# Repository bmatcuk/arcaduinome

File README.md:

# arcaduinome
Arcaduinome is an [Arduino](http://www.arduino.cc/) based MIDI controller that uses arcade buttons for input. The name is a combination of Arcade, Arduino, and [Monome](http://monome.org/).

1. [Software](#software)
2. [Hardware](#hardware)
  1. [Schematic](#schematic)
  2. [Board PCB Layout](#board-pcb-layout)
3. [Arduino Firmware](#arduino-firmware)
4. [License](#license)

## Software
The ArduinoSketch directory contains the Arduino source code. It requires that you have the MIDI Library installed. The latest build (at time of writing) is included in this repo. You'll first need to install it into your Arduino app: Open the Arduino application and select Sketch -> Import Library -> Add Library, then select Arduino_MIDI_Library_v4.1.zip.

## Hardware
Arcaduinome is based around the [Arduino Uno](http://arduino.cc/en/Main/ArduinoBoardUno), third revision. Most of the other hardware components are to support the LEDs which light the arcade buttons. Each component links to a website where you could buy the part, but you can probably find most of these parts at a variety of distributors. A lot of these parts could be swapped out for similar parts. I've made some notes below about why I've chosen a specific part and whether or not you can use some other generic part.

Datasheets for some of these parts can be found in the `reference` directory of this repository.

* **[Arduino Uno R3](http://www.adafruit.com/products/50)**
    I highly recommend a 3rd Revision (R3) board here. The R3 board has a larger USB-to-serial microcontroller (Atmega16U2) which will be reprogrammed later. If you have an older R1 or R2 board, you'll need to reprogram the USB-to-serial microcontroller every time you need to switch between MIDI and Arduino mode. Very annoying. With the R3, you just jumper two pins to switch back to Arduino mode.

* **16x [Sanwa OBSC 24 CW](http://www.paradisearcadeshop.com/sanwa-obsc-24mm-translucent-pushbuttons/689-sanwa-obsc-24-cw.html)**
    Any arcade button will do. Sanwa buttons are extremely popular with arcade cabinet and fighting game enthusiasts for their quick response and high-reliability. However, the buttons might be the most expensive part, so you can save a bit with some cheaper buttons. Just make sure they are translucent/transparent.

* **[Protoshield for Arduino](http://www.adafruit.com/products/51)**
    This part is optional. I like using the protoshield to break out the IO pins from the Arduino and it gives me a nice area to solder everything together. Plus, it's compact.

* **16x [Common Anode RGB LEDs](http://www.adafruit.com/products/302)**
    Theoretically, any RGB LEDs will do, as long as they are common-anode. You may need to adjust resistor values depending on the forward voltage of the LEDs you pick. Link goes to a 25-pack that's actually cheaper, I've found, than buying 16 discrete LEDs from other distributors. So save some money and you'll have 9 extra LEDs for your next project! Woot!

* **[Sanken SLA5086 - 5x P-Channel FET Array](http://www.digikey.com/product-search/en?pv606=52&pv69=80&FV=fff40015%2Cfff80346&mnonly=0&newproducts=0&ColumnSort=0&page=1&stock=1&quantity=0&ptm=0&fid=0&pageSize=500)**
    The P-Channel FETs are used on the "high-side" of the LEDs to turn on the "rows". FETs are well-suited for this switching application, specifically P-Channels for the high-side. If every LED in a row is turned on, the high-side switch must be able to source ~0.24A. This part can handle 5A, so no problems there. Additionally, this particular part has a low (logic level) gate-threshold voltage, which means that it should fully "turn on" easily from the Arduino IO pin. All around, a good fit, and the hardest part to find alternatives for, unless you don't mind dealing with surface mount components. We're only going to use 4 of the 5 PFETs in this package, since we only have 4 rows of LEDs. And we're also going to use these rows to multiplex our buttons. This way, we only need to use 4 inputs for the 16 buttons.

* **2x [STMicroelectronics STPIC6D595B1R 8-bit Shift Register](http://www.digikey.com/product-detail/en/STPIC6D595B1R/497-6328-5-ND/1762207)**
    The shift registers are used on the "low-side" of the LEDs to control individual LEDs (ie, the columns). We need 2 of these because we have "12" LEDs per row (each RGB LED is basically like 3 LEDs - we have 4 RGB LEDs per row, so, 4 x 3 = 12). The two ICs are "daisy chained" to make a 16-bit shift register; we just ignore the last 4-bits since we only need 12. Each pin of the shift register must be able to sink 20mA, and, if every LED in the row is "on", the IC as a whole must be able to sink 8 x 20mA = 160mA. This IC can easily handle that with it's open-drain outputs. Additionally, the outputs are latched, which the code takes advantage of.

* **16x [NXP Semiconductors 1N4148,113 Standard Diode](http://www.digikey.com/product-detail/en/1N4148,113/568-1360-1-ND/763357)**
    Use any standard diodes you want, though lower forward voltages are preferable. These are just used to ensure that the buttons don't interfere with each other if you press two at the same time... particularly if they are in different rows.

* **8x [120 Ohm Resistors](http://www.digikey.com/product-detail/en/CFM14JT120R/S120QCT-ND/2617666)**
    Use any standard 120 Ohm resistors you like. These limit current through the green and blue sections of the RGB LEDs. If you use different RGB LEDs, make sure to use appropriate resistors! The RGB LEDs I'm using have a 3.2V forward voltage for the green and blue sections, so these resistors should limit current to somewhere around 15mA.

* **4x [220 Ohm Resistors](http://www.digikey.com/product-detail/en/CF14JT220R/CF14JT220RCT-ND/1830334)**
    Use any standard 220 Ohm resistors you like. These limit current through the red section of the RGB LEDs. If you use different RGB LEDs, make sure to use appropriate resistors! The RGB LEDs I'm using have a 1.8V forward voltage for the red section, so these resistors should limit current to somewhere around 15mA.

* **9x 4.7 kOhm Resistors**
    I had some of these laying around, so I don't have a link for them. The value is not very important, so any value around 4.7k is fine if you happen to have some resistors laying around, too. Though, you shouldn't have any trouble finding them on Digikey (or similar sites). These are just used as pull-up resistors for the Gates of the PFETs, and pull-down resistors for the buttons. The pull-up resistors will cause the PFETs to be shut-off when the circuit is first powered up, and the pull-down resistors will cause the Arduino to read 0's for the buttons until they are pressed. We need 5 of these resistors for the 5 PFETs in our array package (even though we are only using 4 of those PFETs, we want to make sure the 5th is "turned off"), and 4 resistors for the multiplexed buttons.

* **[12-pin SIP Socket](http://www.digikey.com/product-detail/en/643644-3/A29107-ND/294602)**
    Socket for the P-Channel FET Array - if you decide on some other high-side solution, you might not need this.

* **2x [16-pin DIP Socket](http://www.digikey.com/product-detail/en/A16-LC-TR-R/AE9994-ND/821748)**
    Sockets for the low-side shift registers - if you decide on some other low-side solution, you might not need this.

### Schematic

This is the full schematic for the Arcaduinome:

However, due to limitations in the free version of Eagle and the fact that my PCB-manufacturer-of-choice is going to require that I order at least 3 boards anyway, I designed a smaller board that houses 4 buttons, with associated LEDs, resistors, and diodes, and a shift register:

The idea is that four of these boards would be used: the two boards at the "bottom" will house the shift registers. The two boards at the "top" will not have shift registers and, instead, use jumpers to connect to the boards on the "bottom". Similarly, jumpers are used to connect boards from left to right.

These schematics were generated using the free version of [Eagle v7.1](http://www.cadsoftusa.com/). The files are available in the `eagle` directory of this repository.

### Board PCB Layout

This is the layout of the smaller board I designed:

This layout was generated using the free version of [Eagle v7.1](http://www.cadsoftusa.com/). The files are available in the `eagle` directory of this repository.

## Arduino Firmware
The Arduino Uno R3 uses a microcontroller, specifically the Atmega16U2, as a USB-to-Serial adapter. Arcaduinome takes advantage of this fact using the [Moco](http://morecatlab.akiba.coocan.jp/lab/index.php/aruino/midi-firmware-for-arduino-uno-moco/?lang=en) (aka dualMocoLUFA) firmware. The latest version (at the time of writing) is included in this repo as dualMoco.hex. Installing this firmware on the Atmega16U2 will cause the Arduino to appear as a generic MIDI device to Windows/OSX. This way, we won't need any special drivers to interface with Arcaduinome.

To install the firmware into the Atmega16U2, follow the [DFU Programming Directions](http://arduino.cc/en/Hacking/DFUProgramming8U2) on Arduino's website. Once the new firmware has been installed, it will appear as a generic MIDI device when connected to your computer. You will no longer be able to use it as an Arduino (in other words, you won't be able to reprogram it). However, if you want to reenable Arduino mode, disconnect the Arduino from your computer, connect a jumper between pin 4 and 6 on the ICSP header, and reconnect to your computer. It should now appear as a normal Arduino Uno. When you're done reprogramming, disconnect from your computer, remove the jumper, and reconnect - it will now appear as a MIDI device again!

## License
This work is licensed under a [Creative Commons Attribution-NonCommercial-ShareAlike 4.0 International License](http://creativecommons.org/licenses/by-nc-sa/4.0/)

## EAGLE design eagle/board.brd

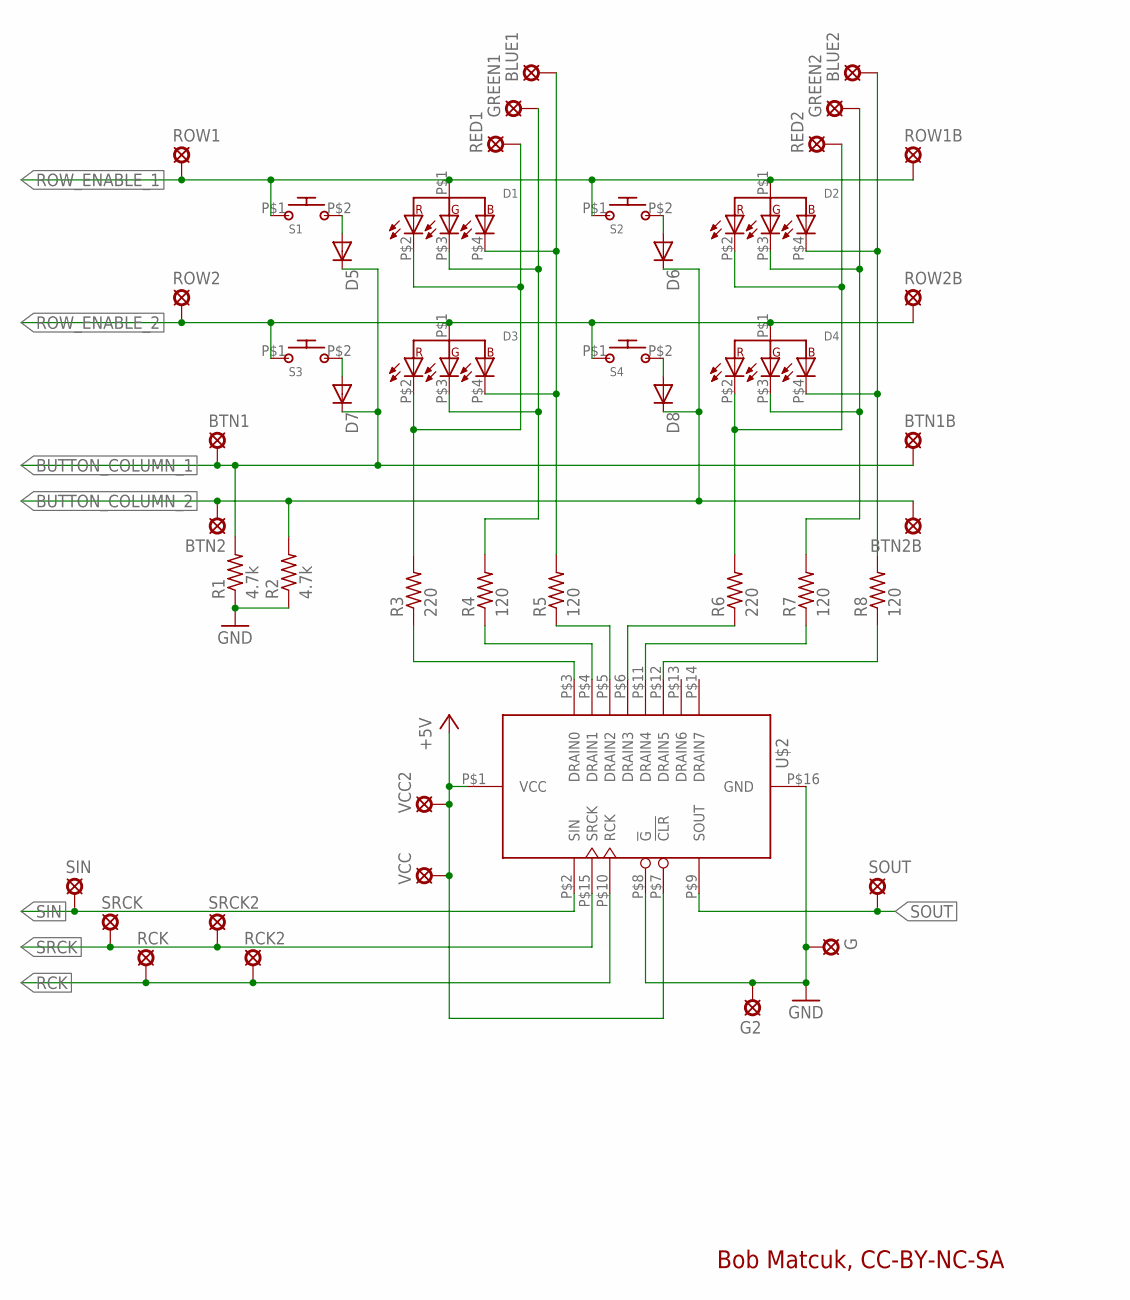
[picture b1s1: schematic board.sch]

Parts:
BLUE1, BLUE2: MCS10B
BTN1, BTN1B, BTN2, BTN2B: MCS10B
D1, D2, D3, D4: FD-5WSRGB-A; 5MM_RGB_LED
D5, D6, D7, D8: 1N4148DO35-7; DO35-7
G, G2: MCS10B
GREEN1, GREEN2: MCS10B
R1, R2: 4.7k; 0207/10
R3, R6: 220; 0207/7
R4, R5, R7, R8: 120; 0204/5
RCK, RCK2: MCS10B
RED1, RED2: MCS10B
ROW1, ROW1B, ROW2, ROW2B: MCS10B
S1, S2, S3, S4: SANWA_OBSC_24_CW; SANWA_24MM
SIN: MCS10B
SOUT: MCS10B
SRCK, SRCK2: MCS10B
U$2: STPIC6D595; DIP16
VCC, VCC2: MCS10B

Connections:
+5V: U$2.P$1 (VCC), U$2.P$7 (!CLR), VCC.MP, VCC2.MP
BUTTON_COLUMN_1: BTN1.MP, BTN1B.MP, D5.C, D7.C, R1.2
BUTTON_COLUMN_2: BTN2.MP, BTN2B.MP, D6.C, D8.C, R2.2
GND: G.MP, G2.MP, R1.1, R2.1, U$2.P$8 (!G), U$2.P$16 (GND)
unnamed: D5.A, S1.P$2
unnamed: D1.P$2 (R), D3.P$2 (R), R3.2, RED1.MP
unnamed: D1.P$3 (G), D3.P$3 (G), GREEN1.MP, R4.2
unnamed: BLUE1.MP, D1.P$4 (B), D3.P$4 (B), R5.2
unnamed: R5.1, U$2.P$5 (DRAIN2)
unnamed: D6.A, S2.P$2
unnamed: R4.1, U$2.P$4 (DRAIN1)
unnamed: D2.P$2 (R), D4.P$2 (R), R6.2, RED2.MP
unnamed: D2.P$3 (G), D4.P$3 (G), GREEN2.MP, R7.2
unnamed: BLUE2.MP, D2.P$4 (B), D4.P$4 (B), R8.2
unnamed: R3.1, U$2.P$3 (DRAIN0)
unnamed: D7.A, S3.P$2
unnamed: D8.A, S4.P$2
unnamed: R6.1, U$2.P$6 (DRAIN3)
unnamed: R7.1, U$2.P$11 (DRAIN4)
unnamed: R8.1, U$2.P$12 (DRAIN5)
RCK: RCK.MP, RCK2.MP, U$2.P$10 (RCK)
ROW_ENABLE_1: D1.P$1 (ANODE), D2.P$1 (ANODE), ROW1.MP, ROW1B.MP, S1.P$1, S2.P$1
ROW_ENABLE_2: D3.P$1 (ANODE), D4.P$1 (ANODE), ROW2.MP, ROW2B.MP, S3.P$1, S4.P$1
SIN: SIN.MP, U$2.P$2 (SIN)
SOUT: SOUT.MP, U$2.P$9 (SOUT)
SRCK: SRCK.MP, SRCK2.MP, U$2.P$15 (SRCK)

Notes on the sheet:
Bob Matcuk, CC-BY-NC-SA

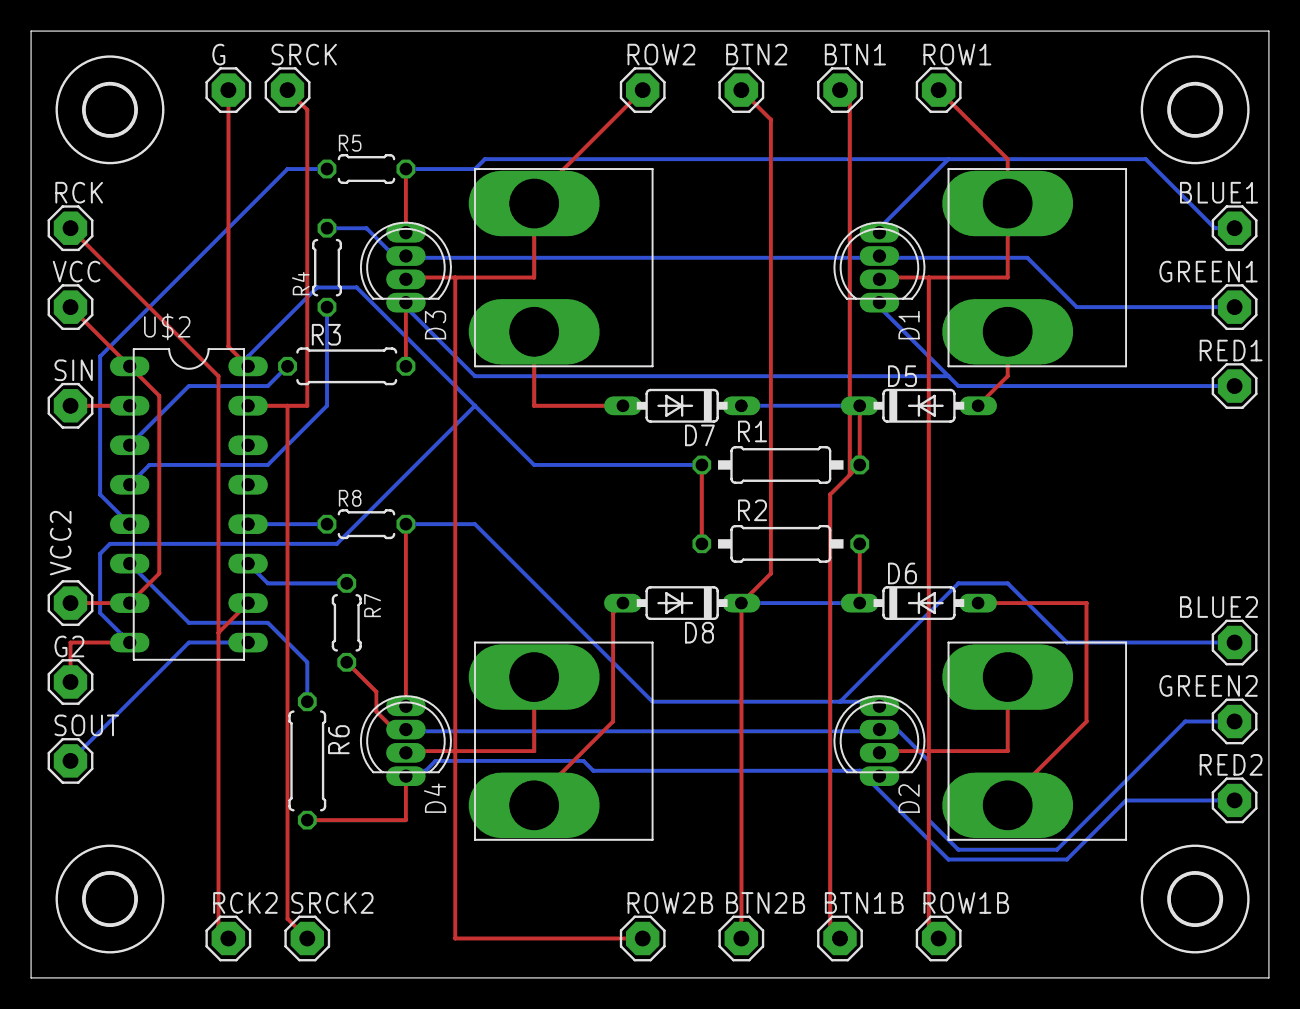
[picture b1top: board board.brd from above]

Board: 2 copper layers, 79.7 x 61.0 mm, 49 parts (0 on the bottom side), 26 nets.

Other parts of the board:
U$3, U$4, U$5, U$6: 3,2

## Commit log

2014-05-30 CC BY-NC-SA
2014-05-30 hardware info
2014-05-30 formatting
2014-06-02 beginning of the Arduino code
2014-06-04 added dualMocoLUFA
2014-06-04 more arduino code
2014-06-06 leds might work? No way to set colors though
2014-06-08 some SPI research - may want to replace SPI library with straight register manipulation for speed
2014-06-09 reference data sheets for arduino, FET array, shift registers, and leds
2014-06-09 reworked SPI to directly access registers for speed
2014-06-10 started some button stuff
2014-06-10 most of the button handling is done - just need to send MIDI commands
2014-06-13 high-side pchannel fets mean we have to pull "low" to turn them on!
2014-07-11 started schematic drawing
2014-07-11 updated SLA5086
2014-07-16 finished SLA5086 component
2014-07-18 added arduino and rgb led compenents; started placing components on schematic
2014-08-07 started eagle schematic
2014-08-08 added SLA5086 symbol and package
2014-08-16 finished SLA5086 and STPIC6D595
2014-08-17 added RGB LEDs
2014-08-17 rearranged shift registers; updated comments
2014-08-17 added resistors
2014-08-17 added Sanwa buttons
2014-08-17 made schematic
2014-08-17 schematic
2014-08-18 removed that kicad nonsense
2014-08-18 added datasheets for resistors and diodes
2014-08-18 added schematic, TOC
2014-08-18 fixed formatting
2014-08-18 small changes
2014-08-26 PCB layout
2014-08-26 updated TOC
2014-10-20 support for setting leds/buttons via sysex; note on/off
